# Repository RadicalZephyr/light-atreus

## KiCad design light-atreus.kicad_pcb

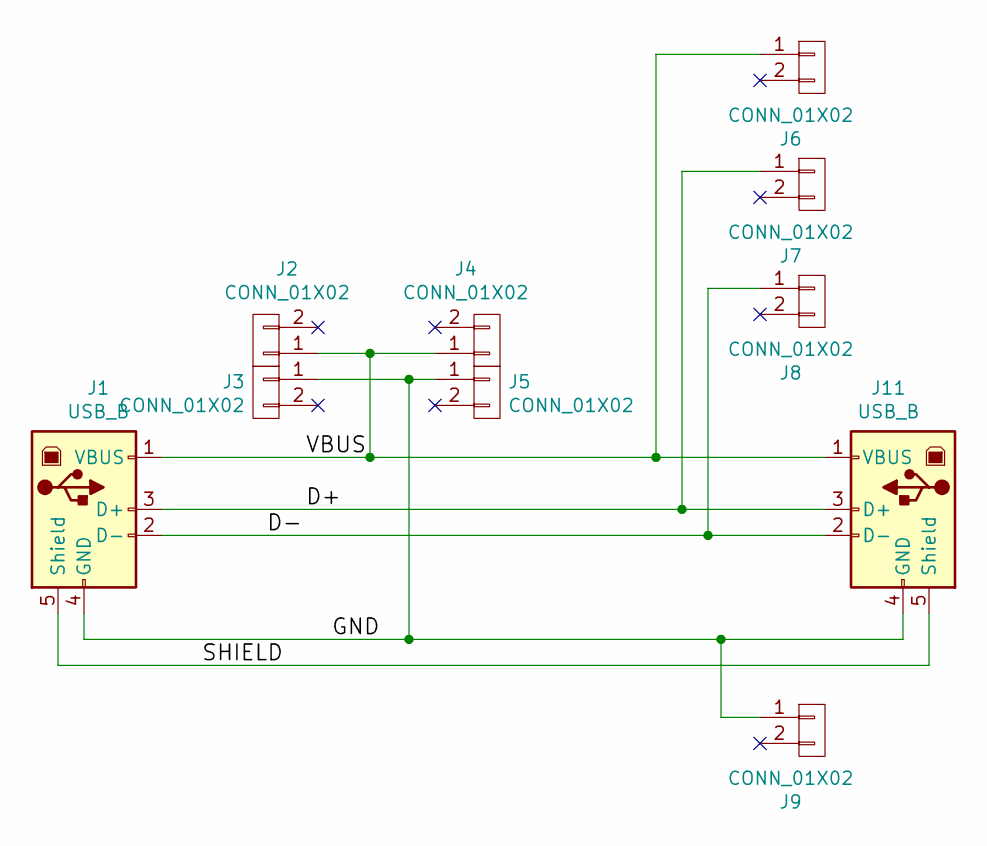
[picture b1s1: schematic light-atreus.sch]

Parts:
J1: USB_B; USB_Micro-B-custom
J2, J3, J4, J5, J6, J7, J8, J9: CONN_01X02; SolderWirePad_1x2-8mm
J11: USB_B; USB_Micro-B-custom-plug

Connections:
/D+: J1.3 (D+), J7.1, J11.3 (D+)
/D-: J1.2 (D-), J8.1, J11.2 (D-)
/GND: J1.4 (GND), J3.1, J5.1, J9.1, J11.4 (GND)
/SHIELD: J1.5 (Shield), J11.5 (Shield)
/VBUS: J1.1 (VBUS), J2.1, J4.1, J6.1, J11.1 (VBUS)

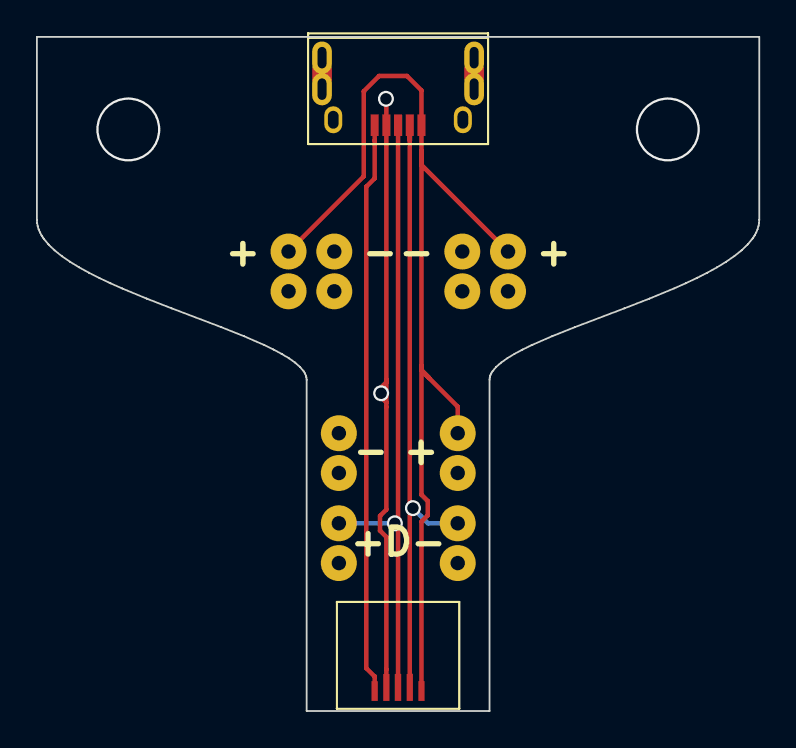
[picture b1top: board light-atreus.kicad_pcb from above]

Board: 2 copper layers, 40.1 x 37.5 mm, 10 parts (0 on the bottom side), 5 nets.

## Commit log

2017-07-31 Add the TUSB320 part to the schematic
2017-09-23 Completely redesign everything
2017-09-23 Use 4-pin connectors for doing fish-hook
2017-09-23 Start creating custom footprint for ZX-62WD1-B-5PC
2017-09-23 Add custom lib to project
2017-09-26 Use stripped version of atreus pcb file as a starting point
2017-09-26 Position mounting holes correctly relative to keys
2017-09-26 Account for using slightly different reference points
2017-09-26 Add actual edge lines
2017-09-26 Use 2x2 instead of 1x4 headers
    That way the arrangement will put the holder hole nearer to the outer
    edge of the board.
2017-09-26 Annotate and generate netlist
2017-09-26 Use banana jack connector pads
2017-09-26 Add custom wire-pad footprint
2017-09-26 Add smaller custom pad
2017-09-26 Roughly place footprints for solder points on board
2017-09-26 Name nets on broken out pins
2017-09-26 Add backside ground pour
2017-09-26 Move wire pads closer together
2017-09-26 Re-place changed wire-pad footprints
2017-09-27 Clean up silk outline of custom USB part
2017-09-28 Finish pad layout for USB receptacle
2017-09-28 Get lower pads to be shaped correctly
2017-09-28 Update schematic for allowing hand-wiring USB plug
2017-09-28 Add a footprint for the ZX64 USB plug
2017-09-28 Regen netlist with correct part footprints
2017-09-28 Add names to all important nets
2017-09-28 Remove initial draft of layout
2017-09-29 Add initial pass at board outline SVG
2017-09-29 Change units to inches
2017-09-29 Convert sizes back to exact in units of inches
2017-09-29 Correct board width and critical coordinates
2017-09-29 Get a properly scaled DXF file
2017-09-29 Start building new board layout with curvy edge
2017-09-29 Place USB pads exactly
2017-09-29 Locate all wire solder points
2017-09-29 Remove shield wire solder point breakout
2017-09-29 Wire USB header traces straight through
2017-09-29 Finish routing the board
2017-09-29 Move all ref des's into the comments layer
2017-09-29 Add some silk labels for upper V+ and GND breakouts
2017-09-29 Add silk labels for inner USB breakout pins
2017-09-29 Add some more trace to the inline ground via
2017-09-29 Shorten board by 7mm to account for USB plug housing
2017-09-29 Reroute traces at new length
2017-09-29 Move LED power breakouts out of the way of the case!
2017-09-29 Route last two V+ traces
2017-09-29 Clean up ugly trace bits
2017-09-29 Correct placement of right +
